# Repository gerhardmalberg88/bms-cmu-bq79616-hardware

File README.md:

# BMS Cell Monitoring Unit (CMU) — Hardware

Supported platform: **Linux**.

Native KiCad 10 design files for the cell-monitoring unit of open-source battery management system. Built around the **Texas Instruments BQ79616-Q1** 16-cell battery monitor, supporting a modular **6S to 16S** stack.

Latest prepared package: **revision 0.1, 16S, exported 2026-11-01**.

- **Manufacturing files:** [package index](manufacturing/rev0.1-2026-11-01/README.md), [complete package ZIP](manufacturing/rev0.1-2026-11-01/complete-package.zip), and [fabrication-only ZIP](manufacturing/rev0.1-2026-11-01/fabrication.zip).
- **KiCad design files:** [schematics, PCB and project files](design/).
- **3D PCB:** [open the latest populated STL](manufacturing/rev0.1-2026-11-01/3d/CMU-rev0.1-16S.stl) in GitHub.
- **COMH/COML EM — reduced CPU study complete; provisional results:** [board-only report](sim/em/report/README.md).
- **Thermal simulations — steady scope complete; provisional results:** [balancing-resistor cases](sim/thermal/README.md).
- **SPICE circuit simulation and model:** [cell voltage input filter](sim/spice/cell-voltage-input-filter/README.md).
- **Mechanical modal and PSD — completed runs; provisional results:** [modal and vibration-response report](sim/mechanical/modal-psd/report/README.md).

<table>
  <tr>
    <th width="50%">PCB — rev 0.1, 16S</th>
    <th width="50%">EM simulation</th>
  </tr>
  <tr>
    <td align="center"></td>
    <td align="center"><br><a href="sim/em/report/README.md">COMH/COML board-only EM results</a></td>
  </tr>
  <tr>
    <th width="50%">Thermal simulation</th>
    <th width="50%">Modal and PSD</th>
  </tr>
  <tr>
    <td align="center"><br><a href="sim/thermal/cell-balancing-resistors/README.md">Automatic balancing: 61.24 °C maximum</a></td>
    <td align="center"><br><a href="sim/mechanical/modal-psd/report/README.md">Modal and PSD: provisional vibration response</a></td>
  </tr>
</table>

**Revision 0.1 — routed prototype, manufacturing package prepared.** The saved
schematic and eight-layer PCB pass the configured ERC and refilled DRC with
zero violations, unconnected items or schematic/PCB mismatches (KiCad 10.0.8,
2026-11-01). This is file-level validation; thermal, SI, fault and hardware
bring-up validation remain open.

The [manufacturing package](manufacturing/rev0.1-2026-11-01/README.md) contains
fabrication, assembly, schematic, mechanical and purchasing files. Purchase
**194 components**: 157 fitted plus all 37 DNP parts retained unfitted. See the
[manufacturing record](docs/CMU-009-manufacturing.md) for acceptance limits.

## Safety warning

This repository is not a certified battery-management product. Lithium battery
systems can cause electric shock, fire, explosion, toxic smoke, severe injury,
property damage, or death. The design has not been certified for functional
safety, automotive use, charging protection, cell balancing, isolation, EMC,
thermal performance, or fault containment. Do not connect it to cells or
manufacture it without an independent schematic, PCB, component, firmware, and
safety review. Use appropriate fusing, current limiting, isolation, enclosure,
fire protection, and supervised test equipment.

## System context

One of three independent repositories:

| Module | Repository | Role |
|---|---|---|
| **CMU** | `bms-cmu-bq79616-hardware` (this one) | BQ79616-Q1 cell monitoring, 6S–16S, no MCU |
| BMU | `bms-bmu-stm32-bq79600-hardware` | STM32H757 + BQ79600-Q1 master, CAN-FD, SoC/SoH |
| BJB | `bms-bjb-bq79631-hardware` | BQ79631-Q1, shunt, contactor and precharge drivers |

The CMU is a slave with no autonomous protection authority. It measures,
balances, reports faults over an isolated daisy chain, and the BMU decides. It
is powered entirely from the cell stack it monitors — there is no external
supply and no way to power it down short of disconnecting its cell taps.

Interfaces are specified in
[`docs/CMU-008-interface-control.md`](docs/CMU-008-interface-control.md), which
the other two repositories cite by tag.

## Design summary

```mermaid
flowchart LR
    CELL["J401 CELL / balancing connector"]
    SENSE["Tap fuses and cell-sense filters"]
    BAL["Passive balancing resistors"]
    POWER["Stack-powered supply and preregulator"]
    BQ["U201 BQ79616-Q1"]
    TEMP["J201 TEMP / GPIO"]
    COMH["T501 isolation transformer / J501 COMH"]
    COML["T502 isolation transformer / J502 COML"]

    CELL --- SENSE --- BQ
    CELL --- BAL --- BQ
    CELL --> POWER --> BQ
    TEMP --- BQ
    BQ <--> COMH
    BQ <--> COML
```

| Item | Value |
|---|---|
| Monitor | BQ79616-Q1, 16 channels, 6S–16S |
| Cell taps | J401 Harwin M80-5002042 fitted; J402/J403 are schematic-only alternatives |
| Tap protection | 17 fitted tap fuses F401–F417; one additional supply fuse F601 |
| Balancing | Passive, 105 mA per channel |
| Temperature | 8 channels via J201; R219–R226 onboard NTC positions DNP |
| Supply | LTC3639 150 V buck to 8.8 V, self-powered from the stack |
| Board draw | up to 16.1 mA from the pack, ACTIVE worst case, balancing excluded |
| Daisy chain | Transformer-isolated COMH/COML |
| Sheets | 7 (root + bq79616, balance, cells, com, batterypositive_to_8V8, mechanical) |
| PCB population | 198 footprints: 157 fitted, 37 DNP, 4 mounting holes |

## Repository layout

```text
bms-cmu-bq79616-hardware/
|-- README.md
|-- LICENSE                     CERN-OHL-P-2.0
|-- LICENSES/
|-- .gitignore
|-- .gitattributes
|-- design/                     authoritative source
|   |-- battery_management_system_cell_monitoring_unit.kicad_pro
|   |-- battery_management_system_cell_monitoring_unit.kicad_sch    root sheet
|   |-- battery_management_system_cell_monitoring_unit.kicad_pcb    routed PCB
|   |-- bq79616.kicad_sch
|   |-- balance.kicad_sch
|   |-- cells.kicad_sch
|   |-- com.kicad_sch
|   |-- batterypositive_to_8V8.kicad_sch
|   |-- mechanical.kicad_sch
|   |-- sym-lib-table
|   |-- fp-lib-table
|   `-- kicad-libraries/        imported parts; README.md is the manifest
|-- docs/                       engineering documentation
|   |-- README.md               index, ordered by phase
|   |-- CMU-001 .. CMU-008      analyses
|   |-- CMU-009-manufacturing.md release and configuration record
|   `-- generated/              exports; never hand-edited
|-- manufacturing/              intentional versioned prototype packages
|-- sim/                        circuit, EM, thermal and mechanical studies
|   |-- README.md               study scope and status
|   |-- spice/                  cell-voltage-input-filter circuit and study
|   |-- em/                     COMH/COML board-only EM cases and reports
|   |-- thermal/                balancing-resistor cases
|   `-- mechanical/             modal and PSD screening; provisional results
`-- tools/
    `-- gen_doc_tables.py       regenerates doc tables from the netlist

Imported-part content identifiers are recorded in design/kicad-libraries/README.md.
No initial upstream commit exists yet; docs/generated/library-provenance.csv records
the present hashes. identify_asset.py can resolve commits once history exists.
```

Files in `design/` are authoritative. Everything in `docs/generated/` is
reproducible output and does not replace the editable source.

## Opening the design

1. Install KiCad 10 with its standard symbol, footprint and 3D-model libraries.
2. Open `design/battery_management_system_cell_monitoring_unit.kicad_pro`.
3. Confirm `custom_symbols` and `custom_footprints` load from the project-local
   tables at `${KIPRJMOD}/kicad-libraries/`.
4. Run ERC. It should report **0 violations**; anything else is a regression.

Standard 3D models resolve through `${KICAD10_3DMODEL_DIR}`. Original models use
`${KIPRJMOD}/kicad-libraries/3d_models/custom_3dmodels.3dshapes/`. No
environment variable or machine-specific absolute path is required.

### Which repositories to clone

`design/kicad-libraries` holds **imported copies of the parts this board uses**,
taken from `github.com/gerhardmalberg/kicad-libraries`. The path is
load-bearing — the library tables and every footprint's 3D reference resolve
through it. It ships with this repository, so most work needs nothing else.

| Task | Clone |
|---|---|
| Use, review, or generate manufacturing files | **This repository only** |
| Design work that needs no new part | **This repository only** |
| Adding a part the board does not have yet | This repository, then `kicad-libraries`; import the part and record it in the manifest |
| Changing a part | This repository, then `kicad-libraries`; **make the change upstream**, commit it there, then re-import |

The last two rows carry the rule that matters. **Never edit
`design/kicad-libraries` in place** — a change made here is invisible to every
other board, and saving a file through the KiCad editor rewrites its UUIDs and
generator string, which breaks identification with no design change.

It holds only what the board uses: 5 symbols, 21 footprints and 12 models. Carrying the rest would mean re-importing whenever a
part belonging to a different board changed.

After placing a symbol that is not in the project library yet, rebuild it from
the schematics rather than copying by hand or saving through the symbol editor:

```console
python ../kicad-libraries/tools/build_symbol_library.py --used-by design \
    --output design/kicad-libraries/symbols/custom_symbols.kicad_sym
```

Copy the part's footprint and model across as well, then add all three to the
manifest. `--check` instead of writing reports whether the library has drifted
from its sources.

Upstream, each symbol is its own library — `ltc3639:LTC3639`. This
project keeps a single `custom_symbols` library of imported copies, so its
`lib_id`s stay stable no matter how the upstream library is organised. The
symbol blocks are copied without a byte changed, so each still identifies
against the file it came from.

### Which library version each part came from

No version number is recorded in any asset. Git names every object by the SHA-1
of its contents, so the content *is* the version.
[`design/kicad-libraries/README.md`](design/kicad-libraries/README.md) is both
the licence notice and the import manifest, listing every file with the upstream
commit and blob it came from. To check the whole set against the library:

```console
python ../kicad-libraries/tools/identify_asset.py \
    --upstream ../kicad-libraries --manifest design/kicad-libraries/README.md
```

Every asset should report `EXACT`. `EQUIVALENT` means the design still matches
but the bytes do not — an editor save or a KiCad format migration rather than a
design change. `DIVERGED` means a part was genuinely edited; re-run with
`--show-diff` to see what. Exits 0 when everything is identified, 1 when
anything diverged, 2 when anything is not from that library, 3 when the upstream
path is not a git repository. Run it before a release.

The three methods, and the two things that break them, are documented once, in
the [library README](https://github.com/gerhardmalberg/kicad-libraries#version-checking).
They are not repeated here.

## Documentation

[`docs/`](docs/) holds the engineering documentation, ordered by phase rather
than by number, because several analyses are *inputs* to layout rather than
descriptions of it:

- **Pre-layout** — requirements, interface control, power budget, FMEA,
  stress/WCCA, layout constraints
- **Post-layout** — thermal, signal integrity
- **Manufacturing** — release, configuration and open confirmations; design
  decisions are recorded in the analyses they affect

Start at [`docs/README.md`](docs/README.md).

Component `Description` fields in the schematic carry the reasoning behind
individual part choices. The documents cite designators and summarise rather
than duplicating that text, so each fact has one source.

## Revision and configuration control

The title block on all seven sheets is driven by **text variables defined once**
in the `.kicad_pro`: `BOARD_TITLE`, `REV`, `ISSUE_DATE`, `ORG`, `LICENSE`,
`COPYRIGHT`, `SOURCE`, `MODULE`. KiCad 10 does not inherit title-block fields
from the root sheet, so this is the only single-source mechanism available.
Bump a revision by editing one file.

Revision scheme: **`0.x`** while unfabricated, **`A`, `B`, `C`** for each
fabricated board. Each release should carry a matching annotated git tag.

Reference designators use per-sheet hundreds blocks — `bq79616` 200, `balance`
300, `cells` 400, `com` 500, `batterypositive_to_8V8` 600 — so a designator
names its page and adding parts to one sheet never renumbers another.

## Manufacturing

The current package is [`manufacturing/rev0.1-2026-11-01/`](manufacturing/rev0.1-2026-11-01/README.md).
It targets Eurocircuits and the current 16S assembly, retaining revision 0.1.
`fabrication.zip` contains only bare-board production data and fabrication
instructions. `complete-package.zip` also includes assembly, purchasing,
schematic PDF, STEP/STL and verification records.

See [`docs/CMU-009-manufacturing.md`](docs/CMU-009-manufacturing.md) for the
repeatable export commands, population rules and open confirmations. View the
[populated STL](manufacturing/rev0.1-2026-11-01/3d/CMU-rev0.1-16S.stl) directly
in GitHub's 3D viewer. The binary mesh is below 10 MB and must remain a normal
Git file for that viewer.

This local package has no source commit/tag because the repository has no
initial commit. Exact source SHA-256 hashes and a source snapshot identify it.
A published immutable release should subsequently identify a reviewed commit
and annotated tag. Never silently replace files in a published release.

## Licensing

Copyright (C) 2021-2026 Gerhard Malberg.

**Everything in this repository is CERN-OHL-P-2.0** — the hardware design, the
KiCad project, the schematics, the PCB, the engineering documentation under
`docs/`, the simulation material under `sim/`, and the imported component
library in `design/kicad-libraries/`. The licence text is in `LICENSE` and
`LICENSES/CERN-OHL-P-2.0.txt`, and `design/kicad-libraries/README.md` carries
the notice for the imported parts rather than a second copy of the text.

[NOTICE.md](NOTICE.md) records the applicable copyright, provenance and
third-party notices, which also accompany the standalone manufacturing archives.

The one exception is content this repository does not own: KiCad's stock symbols
and footprints, used for standard passives and embedded into the `.kicad_sch`
and `.kicad_pcb`, remain CC BY-SA 4.0 with the KiCad library exception. That
exception exists precisely to allow their use in a design without the design
inheriting CC BY-SA. Their texts are in `LICENSES/`.

A permissive licence throughout means the library can be shared across all three
BMS modules and `bldc-controller-hardware` without forcing terms onto anyone who
builds on it, and there is no boundary inside the repository where one licence
stops and another starts.

Commercial manufacture and modification are permitted under CERN-OHL-P-2.0.
These notes are conservative project metadata, not legal advice.

## Third-party content

The design uses KiCad's stock symbol and footprint libraries for standard
passives, which KiCad embeds into the `.kicad_sch` and `.kicad_pcb`. These are
CC BY-SA 4.0 with the KiCad library exception, and that exception permits use in
a design without the design inheriting CC BY-SA.

Every imported part in `design/kicad-libraries/` is CERN-OHL-P-2.0 original
work with no third-party CAD content. Which upstream commit each came from is
recorded in
[`design/kicad-libraries/README.md`](design/kicad-libraries/README.md); the
upstream asset-level register, one row per symbol, footprint, model and source,
stays in the `kicad-libraries` repository rather than being copied here.

Manufacturer datasheets are referenced by URL from each component's `Datasheet`
field. No third-party document is redistributed with this repository.

Manufacturer, distributor, product and service names are trademarks of their
respective owners. Their use is descriptive and implies no affiliation or
endorsement.

## Contribution and release rules

- Do not change circuit connectivity, footprints, stack-up, routing, zones, or
  board outline in a formatting-only commit.
- Add source, author, licence, modification and redistribution evidence for
  every non-standard library asset, in the same commit.
- Keep the four sourcing fields named exactly `MPN`, `digikey_pn`, `MPN_alt`,
  `digikey_pn_alt`. Inconsistent capitalisation splits BOM columns.
- Do not commit KiCad backups, locks, caches, session files or scratch output
  under `build/`. Intentional versioned files under `manufacturing/`, including
  the STL preview, and regenerated `docs/generated/` are permitted.
  `.kicad_prl` remains per-user UI state and is ignored.
- Regenerate `docs/generated/` whenever a reviewed design change is released,
  and run `python tools/gen_doc_tables.py --check` so documentation tables
  cannot drift from the schematic.
- **Close KiCad before scripted edits.** KiCad writes whole sheets from its
  in-memory copy on save and will silently discard external changes.
- Reannotating invalidates every designator cited by name in documentation and
  schematic text. Rewrite those citations in the same operation.
- Record ERC and DRC tool versions and results. Do not hide violations without
  dated engineering rationale in the affected analysis and the manufacturing record.

## No warranty

The design and documentation are provided as-is, without warranties of
correctness, merchantability, fitness for a particular purpose, safety,
non-infringement, or regulatory compliance. To the extent permitted by law, the
contributors disclaim liability for any loss, injury, fire, battery damage,
product failure, or other consequence arising from use, manufacture,
modification, or distribution.

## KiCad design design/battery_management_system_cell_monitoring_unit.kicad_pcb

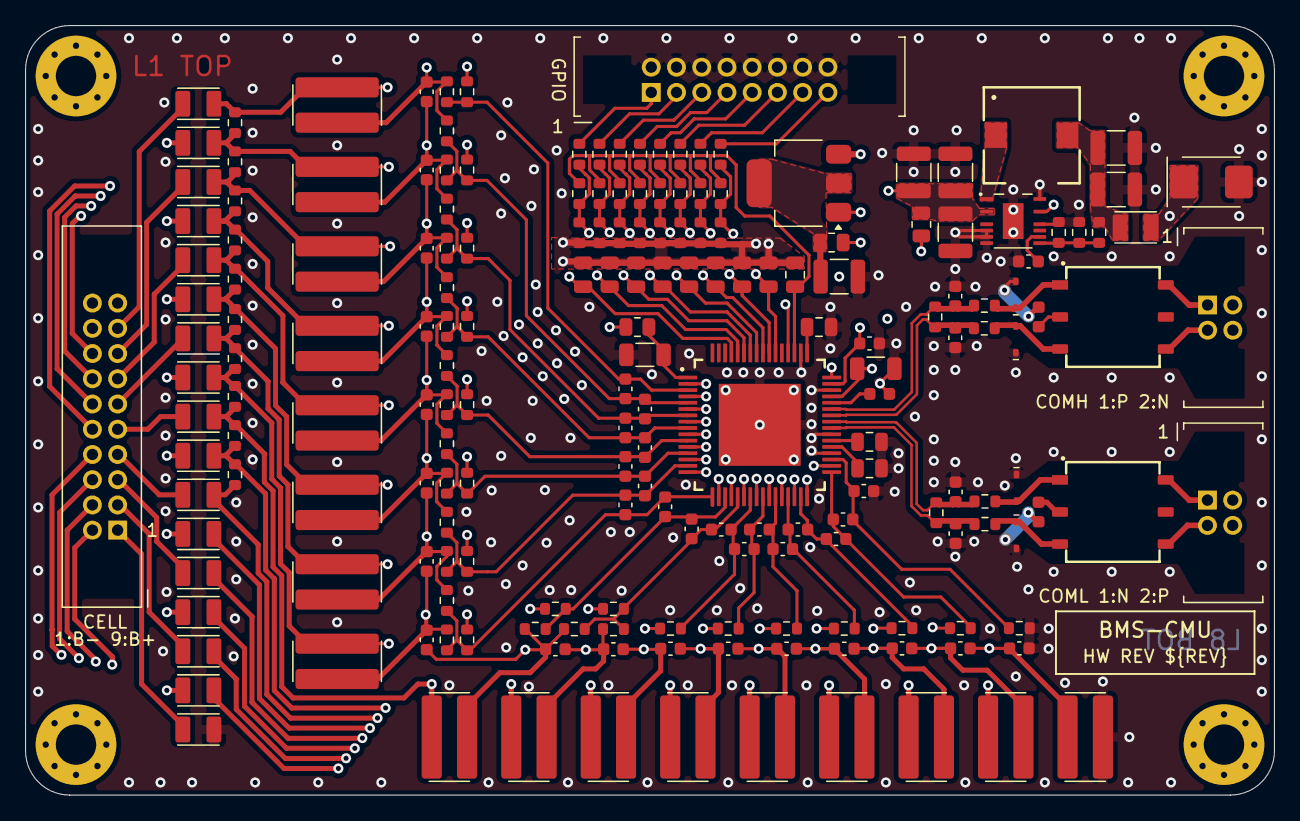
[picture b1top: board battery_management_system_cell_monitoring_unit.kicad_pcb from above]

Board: 8 copper layers, 99.0 x 61.0 mm, 198 parts (0 on the bottom side), 114 nets.

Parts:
C201: 4.7uF 25V X7R; C_1206_3216Metric_OneSideSilkscreen
C202: 2.2uF 25V X7R; C_0805_2012Metric
C203, C204, C209: 1uF 25V X7R; C_0805_2012Metric
C205: 100nF 50V X7R; C_0603_1608Metric_NoSilkscreenBody
C206, C606: 100nF 50V X7R; C_0603_1608Metric
C207: 1uF 100V X7R; C_1210_3225Metric
C208: 10nF 250V C0G; C_1206_3216Metric
C210, C211, C212, C213, C214, C215, C216, C217: 1uF 25V X7R; C_0805_2012Metric_NoSilkscreenBody
C301, C302, C303, C304, C305, C306, C307, C308, C309, C310, C311, C312, C313, C314, C315, C316, C317, C318, C319, C320, C321, C322, C323, C324, C325, C326, C327, C328, C329, C330, C331, C332, C333, C334: 470nF 25V; C_0603_1608Metric
C501, C503, C504, C506: 220pF 50V C0G; C_0603_1608Metric
C502, C505: 100pF 50V C0G; C_0603_1608Metric_NoSilkscreenBody
C601, C602: 4.7uF 100V X7S; C_1210_3225Metric
C603, C604, C605: 100nF 250V X7R; C_1210_3225Metric
D501, D502, D503, D504: CDSOD323-T15C; Bourns_CDSOD323-TxxC_SOD-323_Compact_MinimalSilkscreen
D601: 12V 600W TVS; Bourns_SMBJ-Q_DO-214AA
F401, F402, F403, F404, F405, F406, F407, F408, F409, F410, F411, F412, F413, F414, F415, F416, F417, F601: 500mA 125V FF; Littelfuse_470-Series_Fuse_1206
H1, H2, H3, H4: MountingHole_Pad; MountingHole_3.2mm_M3_Pad_Via
J201: Conn_02x08_Top_Bottom; Harwin_Datamate_M80-5001642_2x08_P2.00mm_Vertical_MinimalSi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
J401: Conn_02x10_Top_Bottom; Harwin_Datamate_M80-5002042_2x10_P2.00mm_Vertical
J501, J502: Conn_02x02_Top_Bottom; Harwin_Datamate_M80-5T10442MC_2x02_P2.00mm_Vertical_Minimal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
L601: 220uH; L_Wuerth_WE-PD-Robust-7332_MinimalSilkscreen
Q201: NPN 100V 2A SOT-223; SOT-223-3_TabPin2
R201, R601: 4R7 1%; R_0805_2012Metric
R202: 30R 1%; R_0805_2012Metric
R203, R204, R205, R206, R207, R208, R209, R210: 10k 0.1%; R_0603_1608Metric
R211, R212, R213, R214, R215, R216, R217, R218, R502, R505: 1k 1%; R_0603_1608Metric
R219, R220, R221, R222, R223, R224, R225, R226: 10k NTC; R_0603_1608Metric_NoSilkscreenBody
R301, R306, R307, R315, R316, R322, R323, R329, R330, R336, R337, R343, R344, R350, R351, R357, R358: 100R 0.1%; R_0603_1608Metric
R302, R303, R305, R308, R309, R310, R311, R314, R317, R318, R321, R324, R325, R328, R331, R332, R335, R338, R339, R342, R345, R346, R349, R352, R353, R356, R359, R360: 0R; R_0603_1608Metric
R304, R312, R313, R319, R320, R326, R327, R333, R334, R340, R341, R347, R348, R354, R355, R361, R362: 20R 2W; Vishay_RCL1225_2W_3.2x6.3mm
R501, R503, R504, R506: 49R9 1%; R_0603_1608Metric
R602: 1M8 1%; R_0603_1608Metric
R603: 180k 0.1%; R_0603_1608Metric
R604: 620k 1%; R_0603_1608Metric
T501, T502: SM91502AL
U201: BQ79616-Q1
U601: LTC3639; LTC3639_MSE16-12_MinimalSilkscreen

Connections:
+8V8: D601.1 (K), F601.2, R201.1
+BATT: F401.2, R202.1, R307.1, R310.2, R313.1, R601.1
/balance/CB0: C327.2, C331.1, R361.2, U201.34 (CB0)
/balance/CB1: C323.2, C327.1, R354.2, U201.32 (CB1)
/balance/CB2: C319.2, C323.1, R347.2, U201.30 (CB2)
/balance/CB3: C315.2, C319.1, R340.2, U201.28 (CB3)
/balance/CB4: C311.2, C315.1, R333.2, U201.26 (CB4)
/balance/CB5: C307.2, C311.1, R326.2, U201.24 (CB5)
/balance/CB6: C303.2, C307.1, R319.2, U201.22 (CB6)
/balance/CB7: C301.2, C303.1, R309.1, R312.2, U201.20 (CB7)
/balance/CB8: C301.1, C333.2, R303.1, R304.2, R305.2, U201.18 (CB8)
/balance/CB9: C329.2, C333.1, R360.1, R362.2, U201.16 (CB9)
/balance/CB10: C325.2, C329.1, R353.1, R355.2, R356.2, U201.14 (CB10)
/balance/CB11: C321.2, C325.1, R346.1, R348.2, R349.2, U201.12 (CB11)
/balance/CB12: C317.2, C321.1, R339.1, R341.2, R342.2, U201.10 (CB12)
/balance/CB13: C313.2, C317.1, R332.1, R334.2, R335.2, U201.8 (CB13)
/balance/CB14: C309.2, C313.1, R325.1, R327.2, R328.2, U201.6 (CB14)
/balance/CB15: C305.2, C309.1, R318.1, R320.2, R321.2, U201.4 (CB15)
/balance/CB16: C305.1, R311.1, R313.2, R314.2, U201.2 (CB16)
/balance/VC0: C328.2, C332.1, R357.2, U201.35 (VC0)
/balance/VC1: C324.2, C328.1, R350.2, U201.33 (VC1)
/balance/VC2: C320.2, C324.1, R343.2, U201.31 (VC2)
/balance/VC3: C316.2, C320.1, R336.2, U201.29 (VC3)
/balance/VC4: C312.2, C316.1, R329.2, U201.27 (VC4)
/balance/VC5: C308.2, C312.1, R322.2, U201.25 (VC5)
/balance/VC6: C304.2, C308.1, R315.2, U201.23 (VC6)
/balance/VC7: C302.2, C304.1, R305.1, R306.2, R309.2, U201.21 (VC7)
/balance/VC8: C302.1, C334.2, R301.2, R303.2, U201.19 (VC8)
/balance/VC9: C330.2, C334.1, R356.1, R358.2, R360.2, U201.17 (VC9)
/balance/VC10: C326.2, C330.1, R349.1, R351.2, R353.2, U201.15 (VC10)
/balance/VC11: C322.2, C326.1, R342.1, R344.2, R346.2, U201.13 (VC11)
/balance/VC12: C318.2, C322.1, R335.1, R337.2, R339.2, U201.11 (VC12)
/balance/VC13: C314.2, C318.1, R328.1, R330.2, R332.2, U201.9 (VC13)
/balance/VC14: C310.2, C314.1, R321.1, R323.2, R325.2, U201.7 (VC14)
/balance/VC15: C306.2, C310.1, R314.1, R316.2, R318.2, U201.5 (VC15)
/balance/VC16: C306.1, R307.2, R311.2, U201.3 (VC16)
/balance/cell1: F416.2, R350.1, R354.1
/balance/cell2: F415.2, R343.1, R347.1
/balance/cell3: F414.2, R336.1, R340.1
/balance/cell4: F413.2, R329.1, R333.1
/balance/cell5: F412.2, R322.1, R326.1
/balance/cell6: F411.2, R308.1, R315.1, R319.1
/balance/cell7: F410.2, R302.1, R306.1, R308.2, R312.1
/balance/cell8: F409.2, R301.1, R302.2, R304.1, R359.1
/balance/cell9: F408.2, R352.1, R358.1, R359.2, R362.1
/balance/cell10: F407.2, R345.1, R351.1, R352.2, R355.1
/balance/cell11: F406.2, R338.1, R344.1, R345.2, R348.1
/balance/cell12: F405.2, R331.1, R337.1, R338.2, R341.1
/balance/cell13: F404.2, R324.1, R330.1, R331.2, R334.1
/balance/cell14: F403.2, R317.1, R323.1, R324.2, R327.1
/balance/cell15: F402.2, R310.1, R316.1, R317.2, R320.1
/bq79616/COMHN: C503.1, R502.2, R503.1, U201.42 (COMHN)
/bq79616/COMHP: C501.2, R501.1, R502.1, U201.43 (COMHP)
/bq79616/COMLN: C506.1, R505.2, R506.1, U201.41 (COMLN)
/bq79616/COMLP: C504.2, R504.1, R505.1, U201.40 (COMLP)
/com/FILT_COMHN: D502.2 (A2), R503.2, T501.3 (PRI-)
/com/FILT_COMHP: D501.1 (A1), R501.2, T501.1 (PRI+)
/com/FILT_COMLN: D504.2 (A2), R506.2, T502.1 (PRI+)
/com/FILT_COMLP: D503.1 (A1), R504.2, T502.3 (PRI-)
/com/ISO_COMHN: J501.2, T501.4 (LINE-)
/com/ISO_COMHP: J501.1, T501.6 (LINE+)
/com/ISO_COMLN: J502.1, T502.6 (LINE+)
/com/ISO_COMLP: J502.2, T502.4 (LINE-)
GND: C201.1, C202.1, C203.1, C204.1, C205.1, C206.1, C207.1, C208.2, C209.1, C210.1, C211.1, C212.1, C213.1, C214.1, C215.1, C216.1, C217.1, C331.2, C332.2, C501.1, C502.2, C503.2, C504.1, C505.2, C506.2, C601.2, C602.2, C603.2, C604.2, C605.2, C606.2, D501.2 (A2), D502.1 (A1), D503.2 (A2), D504.1 (A1), D601.2 (A), F417.2, J201.9, J201.10, J201.11, J201.12, J201.13, J201.14, J201.15, J201.16, R219.2, R220.2, R221.2, R222.2, R223.2, R224.2, R225.2, R226.2, R357.1, R361.1, R603.2, R604.2, U201.36 (REFHM), U201.39 (AVSS), U201.46 (CVSS), U201.50 (DVSS), U201.65 (EP), U601.6 (VPRG2), U601.7 (VPRG1), U601.8 (GND), U601.12 (OVLO), U601.16 (GND), U601.17 (GND)
unnamed: C601.1, C602.1, F601.1, L601.2, R602.1
unnamed: J201.1, R211.2
unnamed: J201.2, R212.2
unnamed: J201.3, R213.2
unnamed: J201.4, R214.2
unnamed: J201.5, R215.2
unnamed: J201.6, R216.2
unnamed: J201.7, R217.2
unnamed: J201.8, R218.2
unnamed: F417.1, J401.1
unnamed: F415.1, J401.2
unnamed: F413.1, J401.3
unnamed: F411.1, J401.4
unnamed: F409.1, J401.5
unnamed: F407.1, J401.6
unnamed: F405.1, J401.7
unnamed: F403.1, J401.8
unnamed: F401.1, J401.9
unnamed: F416.1, J401.11
unnamed: F414.1, J401.12
unnamed: F412.1, J401.13
unnamed: F410.1, J401.14
unnamed: F408.1, J401.15
unnamed: F406.1, J401.16
unnamed: F404.1, J401.17
unnamed: F402.1, J401.18
unnamed: Q201.1 (B), U201.48 (NPNB)
unnamed: C207.2, Q201.2 (C), R201.2
unnamed: C206.2, Q201.3 (E), U201.47 (LDOIN)
unnamed: C502.1, T501.2 (PR_CT)
unnamed: C505.1, T502.2 (PR_CT)
unnamed: C204.2, U201.38 (AVDD)
unnamed: C208.1, R202.2, U201.1 (BAT)
unnamed: C201.2, U201.45 (CVDD), U201.52 (RX)
unnamed: C202.2, U201.49 (DVDD)
unnamed: C217.2, R203.2, R211.1, R219.1, U201.61 (GPIO1)
unnamed: C216.2, R204.2, R212.1, R220.1, U201.60 (GPIO2)
unnamed: C215.2, R205.2, R213.1, R221.1, U201.59 (GPIO3)
unnamed: C214.2, R206.2, R214.1, R222.1, U201.58 (GPIO4)
unnamed: C213.2, R207.2, R215.1, R223.1, U201.57 (GPIO5)
unnamed: C212.2, R208.2, R216.1, R224.1, U201.56 (GPIO6)
unnamed: C211.2, R209.2, R217.1, R225.1, U201.55 (GPIO7)
unnamed: C210.2, R210.2, R218.1, R226.1, U201.54 (GPIO8)
unnamed: C205.2, U201.44 (NEG5V)
unnamed: C203.2, U201.37 (REFHP)
unnamed: C209.2, R203.1, R204.1, R205.1, R206.1, R207.1, R208.1, R209.1, R210.1, U201.51 (TSREF)
unnamed: C603.1, C604.1, C605.1, R601.2, U601.3 (VIN), U601.14 (RUN)
unnamed: C606.1, U601.10 (SS)
unnamed: L601.1, U601.1 (SW)
unnamed: R602.2, R603.1, R604.1, U601.9 (VFB)

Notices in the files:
parts and their libraries:
COPYRIGHT: Copyright (C) 2021-2026 Gerhard Malberg
LICENSE: SPDX-License-Identifier: CERN-OHL-P-2.0
